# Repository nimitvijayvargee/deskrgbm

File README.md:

# deskrgbm
desktop rgb matrix for the vibes

deskrgbm has a xiao-rp2040 and a WS2812B matrix that can be controlled using QMK-Vial. It is a simple RGB Matrix that can display effects and be used as a desktop ornament. It also features a rotary encoder to control the effects, brightness and speed of the RGB Matrix. The code is written in QMK and can be easily modified using the Vial GUI.

The PCB is very easy to assemble and uses THT Capacitors to be beginner friendly. It is a simple 2 Layer board that does not cost too much to manufacture. The holder is designed in a way such that you can easily use heatsunk threaded inserts and M3 screws to hold the PCB in place. It is intended to print in PLA to be cost effective. \

## Bill of Materials

|Product       |Price|Link                                                                                               |
|--------------|-----|---------------------------------------------------------------------------------------------------|
|PCB           |21   |https://lioncircuits.com/                                                                          |
|WS2812B       |5    |https://www.ktron.in/product/ws2812b-rgb-smd-5050-led/                                             |
|THT Capacitors|5    |https://sharvielectronics.com/product/100nf-250v-0-1uf-polyester-film-capacitor-7-5mm              |
|Xiao RP2040   |8    |https://thinkrobotics.com/products/seeed-studio-xiao-rp2040                                        |
|Rotary encoder|3    |https://amzn.in/d/0EOqh1U                                                                          |
|Total         |42   |                                                                                                   |

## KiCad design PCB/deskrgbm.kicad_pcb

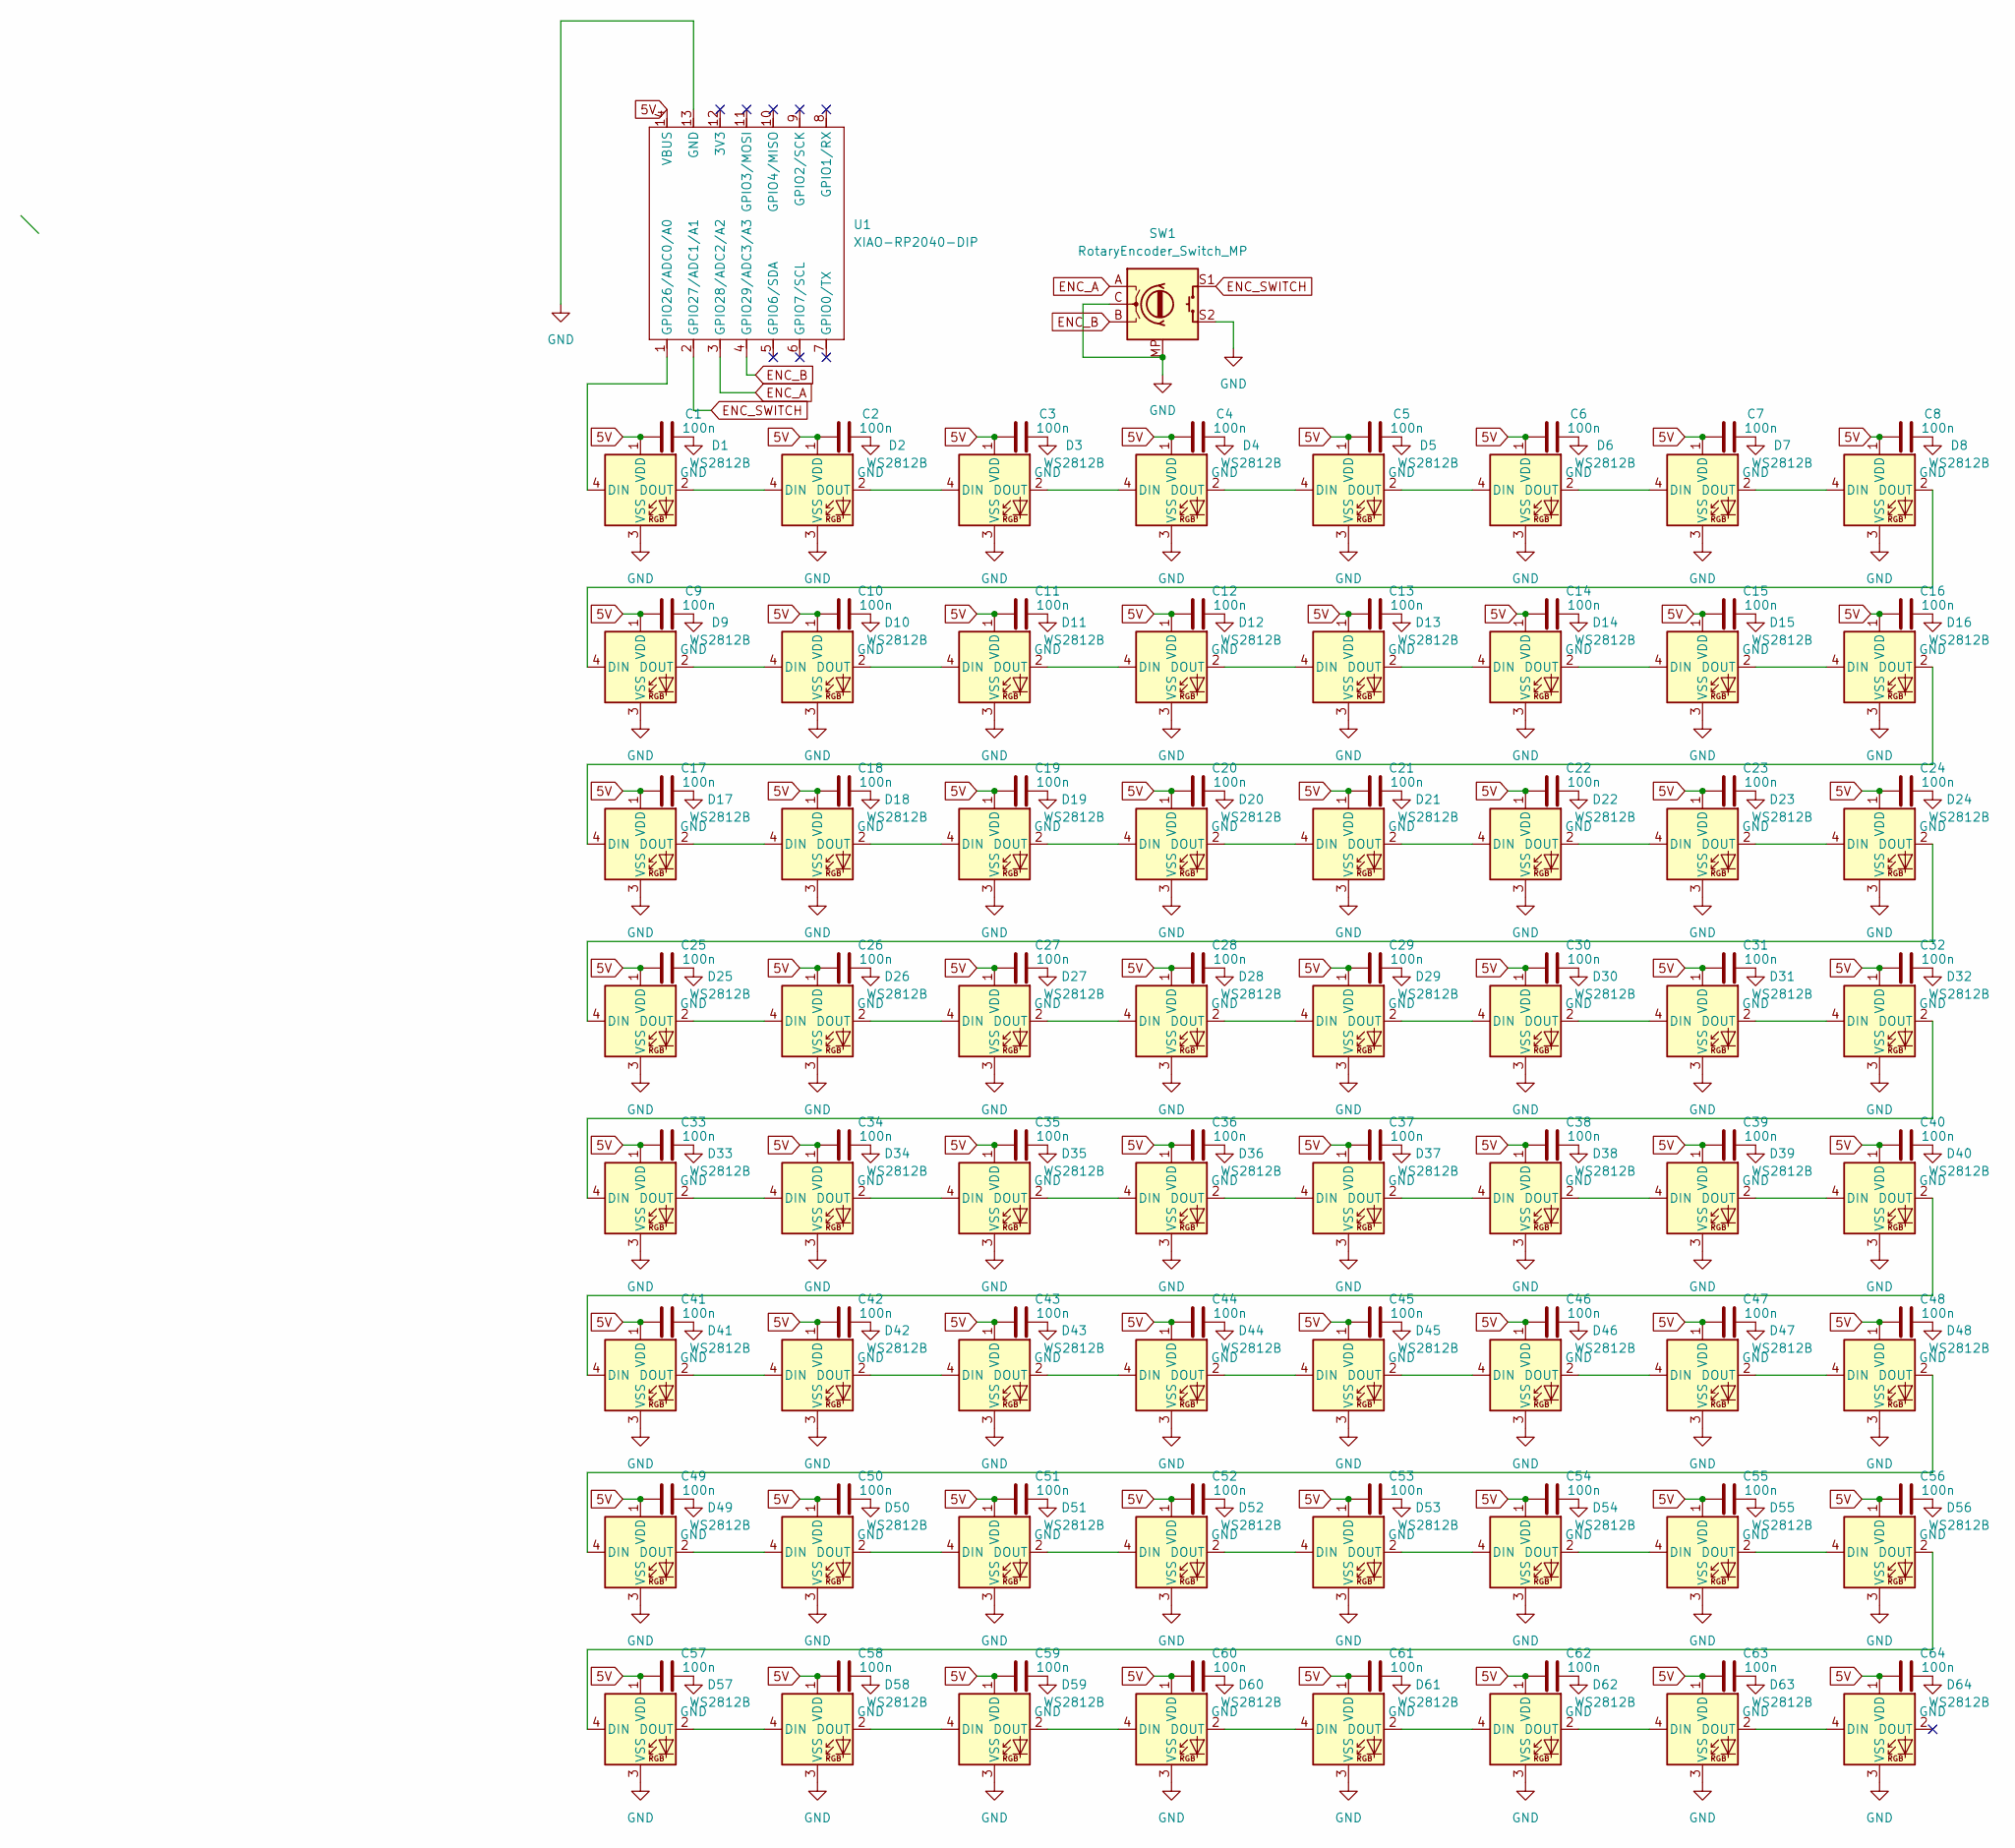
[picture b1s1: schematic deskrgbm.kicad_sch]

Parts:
C1, C2, C3, C4, C5, C6, C7, C8, C9, C10, C11, C12, C13, C14, C15, C16, C17, C18, C19, C20, C21, C22, C23, C24, C25, C26, C27, C28, C29, C30, C31, C32, C33, C34, C35, C36, C37, C38, C39, C40, C41, C42, C43, C44, C45, C46, C47, C48, C49, C50, C51, C52, C53, C54, C55, C56, C57, C58, C59, C60, C61, C62, C63, C64: 100n; C_Disc_D3.0mm_W1.6mm_P2.50mm
D1, D2, D3, D4, D5, D6, D7, D8, D9, D10, D11, D12, D13, D14, D15, D16, D17, D18, D19, D20, D21, D22, D23, D24, D25, D26, D27, D28, D29, D30, D31, D32, D33, D34, D35, D36, D37, D38, D39, D40, D41, D42, D43, D44, D45, D46, D47, D48, D49, D50, D51, D52, D53, D54, D55, D56, D57, D58, D59, D60, D61, D62, D63, D64: WS2812B; LED_WS2812B_PLCC4_5.0x5.0mm_P3.2mm
SW1: RotaryEncoder_Switch_MP; RotaryEncoder_Alps_EC11E-Switch_Vertical_H20mm_MountingHoles
U1: XIAO-RP2040-DIP

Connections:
5V: C1.2, C2.2, C3.2, C4.2, C5.2, C6.2, C7.2, C8.2, C9.2, C10.2, C11.2, C12.2, C13.2, C14.2, C15.2, C16.2, C17.2, C18.2, C19.2, C20.2, C21.2, C22.2, C23.2, C24.2, C25.2, C26.2, C27.2, C28.2, C29.2, C30.2, C31.2, C32.2, C33.2, C34.2, C35.2, C36.2, C37.2, C38.2, C39.2, C40.2, C41.2, C42.2, C43.2, C44.2, C45.2, C46.2, C47.2, C48.2, C49.2, C50.2, C51.2, C52.2, C53.2, C54.2, C55.2, C56.2, C57.2, C58.2, C59.2, C60.2, C61.2, C62.2, C63.2, C64.2, D1.1 (VDD), D2.1 (VDD), D3.1 (VDD), D4.1 (VDD), D5.1 (VDD), D6.1 (VDD), D7.1 (VDD), D8.1 (VDD), D9.1 (VDD), D10.1 (VDD), D11.1 (VDD), D12.1 (VDD), D13.1 (VDD), D14.1 (VDD), D15.1 (VDD), D16.1 (VDD), D17.1 (VDD), D18.1 (VDD), D19.1 (VDD), D20.1 (VDD), D21.1 (VDD), D22.1 (VDD), D23.1 (VDD), D24.1 (VDD), D25.1 (VDD), D26.1 (VDD), D27.1 (VDD), D28.1 (VDD), D29.1 (VDD), D30.1 (VDD), D31.1 (VDD), D32.1 (VDD), D33.1 (VDD), D34.1 (VDD), D35.1 (VDD), D36.1 (VDD), D37.1 (VDD), D38.1 (VDD), D39.1 (VDD), D40.1 (VDD), D41.1 (VDD), D42.1 (VDD), D43.1 (VDD), D44.1 (VDD), D45.1 (VDD), D46.1 (VDD), D47.1 (VDD), D48.1 (VDD), D49.1 (VDD), D50.1 (VDD), D51.1 (VDD), D52.1 (VDD), D53.1 (VDD), D54.1 (VDD), D55.1 (VDD), D56.1 (VDD), D57.1 (VDD), D58.1 (VDD), D59.1 (VDD), D60.1 (VDD), D61.1 (VDD), D62.1 (VDD), D63.1 (VDD), D64.1 (VDD), U1.14 (VBUS)
ENC_A: SW1.A, U1.3 (GPIO28/ADC2/A2)
ENC_B: SW1.B, U1.4 (GPIO29/ADC3/A3)
ENC_SWITCH: SW1.S1, U1.2 (GPIO27/ADC1/A1)
GND: C1.1, C2.1, C3.1, C4.1, C5.1, C6.1, C7.1, C8.1, C9.1, C10.1, C11.1, C12.1, C13.1, C14.1, C15.1, C16.1, C17.1, C18.1, C19.1, C20.1, C21.1, C22.1, C23.1, C24.1, C25.1, C26.1, C27.1, C28.1, C29.1, C30.1, C31.1, C32.1, C33.1, C34.1, C35.1, C36.1, C37.1, C38.1, C39.1, C40.1, C41.1, C42.1, C43.1, C44.1, C45.1, C46.1, C47.1, C48.1, C49.1, C50.1, C51.1, C52.1, C53.1, C54.1, C55.1, C56.1, C57.1, C58.1, C59.1, C60.1, C61.1, C62.1, C63.1, C64.1, D1.3 (VSS), D2.3 (VSS), D3.3 (VSS), D4.3 (VSS), D5.3 (VSS), D6.3 (VSS), D7.3 (VSS), D8.3 (VSS), D9.3 (VSS), D10.3 (VSS), D11.3 (VSS), D12.3 (VSS), D13.3 (VSS), D14.3 (VSS), D15.3 (VSS), D16.3 (VSS), D17.3 (VSS), D18.3 (VSS), D19.3 (VSS), D20.3 (VSS), D21.3 (VSS), D22.3 (VSS), D23.3 (VSS), D24.3 (VSS), D25.3 (VSS), D26.3 (VSS), D27.3 (VSS), D28.3 (VSS), D29.3 (VSS), D30.3 (VSS), D31.3 (VSS), D32.3 (VSS), D33.3 (VSS), D34.3 (VSS), D35.3 (VSS), D36.3 (VSS), D37.3 (VSS), D38.3 (VSS), D39.3 (VSS), D40.3 (VSS), D41.3 (VSS), D42.3 (VSS), D43.3 (VSS), D44.3 (VSS), D45.3 (VSS), D46.3 (VSS), D47.3 (VSS), D48.3 (VSS), D49.3 (VSS), D50.3 (VSS), D51.3 (VSS), D52.3 (VSS), D53.3 (VSS), D54.3 (VSS), D55.3 (VSS), D56.3 (VSS), D57.3 (VSS), D58.3 (VSS), D59.3 (VSS), D60.3 (VSS), D61.3 (VSS), D62.3 (VSS), D63.3 (VSS), D64.3 (VSS), SW1.C, SW1.MP, SW1.S2, U1.13 (GND)
unnamed: D1.4 (DIN), U1.1 (GPIO26/ADC0/A0)
unnamed: D1.2 (DOUT), D2.4 (DIN)
unnamed: D2.2 (DOUT), D3.4 (DIN)
unnamed: D3.2 (DOUT), D4.4 (DIN)
unnamed: D4.2 (DOUT), D5.4 (DIN)
unnamed: D5.2 (DOUT), D6.4 (DIN)
unnamed: D6.2 (DOUT), D7.4 (DIN)
unnamed: D7.2 (DOUT), D8.4 (DIN)
unnamed: D8.2 (DOUT), D9.4 (DIN)
unnamed: D9.2 (DOUT), D10.4 (DIN)
unnamed: D10.2 (DOUT), D11.4 (DIN)
unnamed: D11.2 (DOUT), D12.4 (DIN)
unnamed: D12.2 (DOUT), D13.4 (DIN)
unnamed: D13.2 (DOUT), D14.4 (DIN)
unnamed: D14.2 (DOUT), D15.4 (DIN)
unnamed: D15.2 (DOUT), D16.4 (DIN)
unnamed: D16.2 (DOUT), D17.4 (DIN)
unnamed: D17.2 (DOUT), D18.4 (DIN)
unnamed: D18.2 (DOUT), D19.4 (DIN)
unnamed: D19.2 (DOUT), D20.4 (DIN)
unnamed: D20.2 (DOUT), D21.4 (DIN)
unnamed: D21.2 (DOUT), D22.4 (DIN)
unnamed: D22.2 (DOUT), D23.4 (DIN)
unnamed: D23.2 (DOUT), D24.4 (DIN)
unnamed: D24.2 (DOUT), D25.4 (DIN)
unnamed: D25.2 (DOUT), D26.4 (DIN)
unnamed: D26.2 (DOUT), D27.4 (DIN)
unnamed: D27.2 (DOUT), D28.4 (DIN)
unnamed: D28.2 (DOUT), D29.4 (DIN)
unnamed: D29.2 (DOUT), D30.4 (DIN)
unnamed: D30.2 (DOUT), D31.4 (DIN)
unnamed: D31.2 (DOUT), D32.4 (DIN)
unnamed: D32.2 (DOUT), D33.4 (DIN)
unnamed: D33.2 (DOUT), D34.4 (DIN)
unnamed: D34.2 (DOUT), D35.4 (DIN)
unnamed: D35.2 (DOUT), D36.4 (DIN)
unnamed: D36.2 (DOUT), D37.4 (DIN)
unnamed: D37.2 (DOUT), D38.4 (DIN)
unnamed: D38.2 (DOUT), D39.4 (DIN)
unnamed: D39.2 (DOUT), D40.4 (DIN)
unnamed: D40.2 (DOUT), D41.4 (DIN)
unnamed: D41.2 (DOUT), D42.4 (DIN)
unnamed: D42.2 (DOUT), D43.4 (DIN)
unnamed: D43.2 (DOUT), D44.4 (DIN)
unnamed: D44.2 (DOUT), D45.4 (DIN)
unnamed: D45.2 (DOUT), D46.4 (DIN)
unnamed: D46.2 (DOUT), D47.4 (DIN)
unnamed: D47.2 (DOUT), D48.4 (DIN)
unnamed: D48.2 (DOUT), D49.4 (DIN)
unnamed: D49.2 (DOUT), D50.4 (DIN)
unnamed: D50.2 (DOUT), D51.4 (DIN)
unnamed: D51.2 (DOUT), D52.4 (DIN)
unnamed: D52.2 (DOUT), D53.4 (DIN)
unnamed: D53.2 (DOUT), D54.4 (DIN)
unnamed: D54.2 (DOUT), D55.4 (DIN)
unnamed: D55.2 (DOUT), D56.4 (DIN)
unnamed: D56.2 (DOUT), D57.4 (DIN)
unnamed: D57.2 (DOUT), D58.4 (DIN)
unnamed: D58.2 (DOUT), D59.4 (DIN)
unnamed: D59.2 (DOUT), D60.4 (DIN)
unnamed: D60.2 (DOUT), D61.4 (DIN)
unnamed: D61.2 (DOUT), D62.4 (DIN)
unnamed: D62.2 (DOUT), D63.4 (DIN)
unnamed: D63.2 (DOUT), D64.4 (DIN)

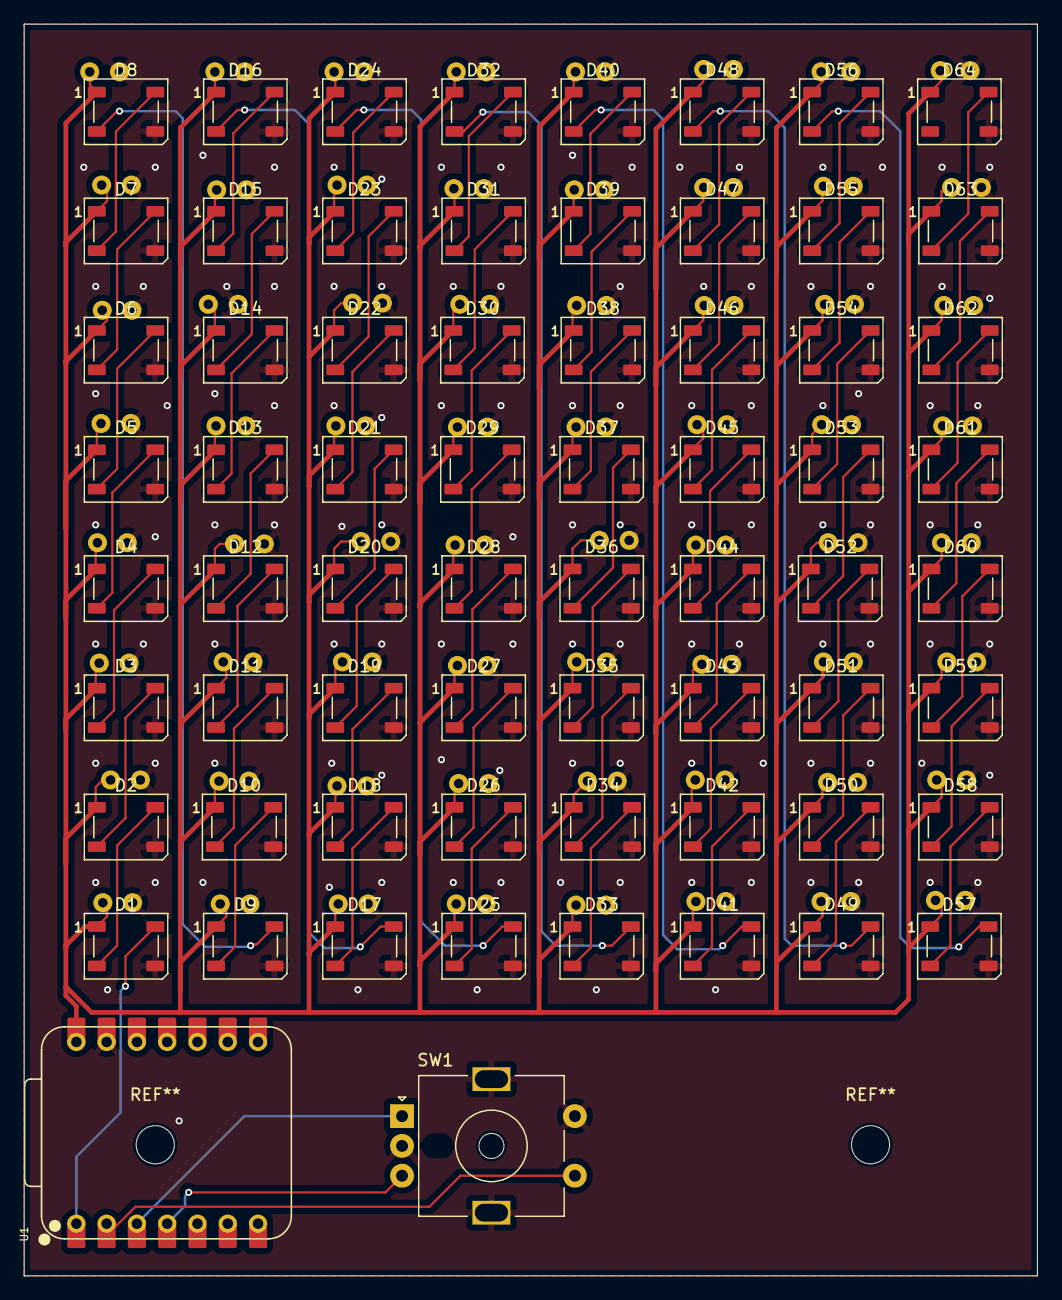
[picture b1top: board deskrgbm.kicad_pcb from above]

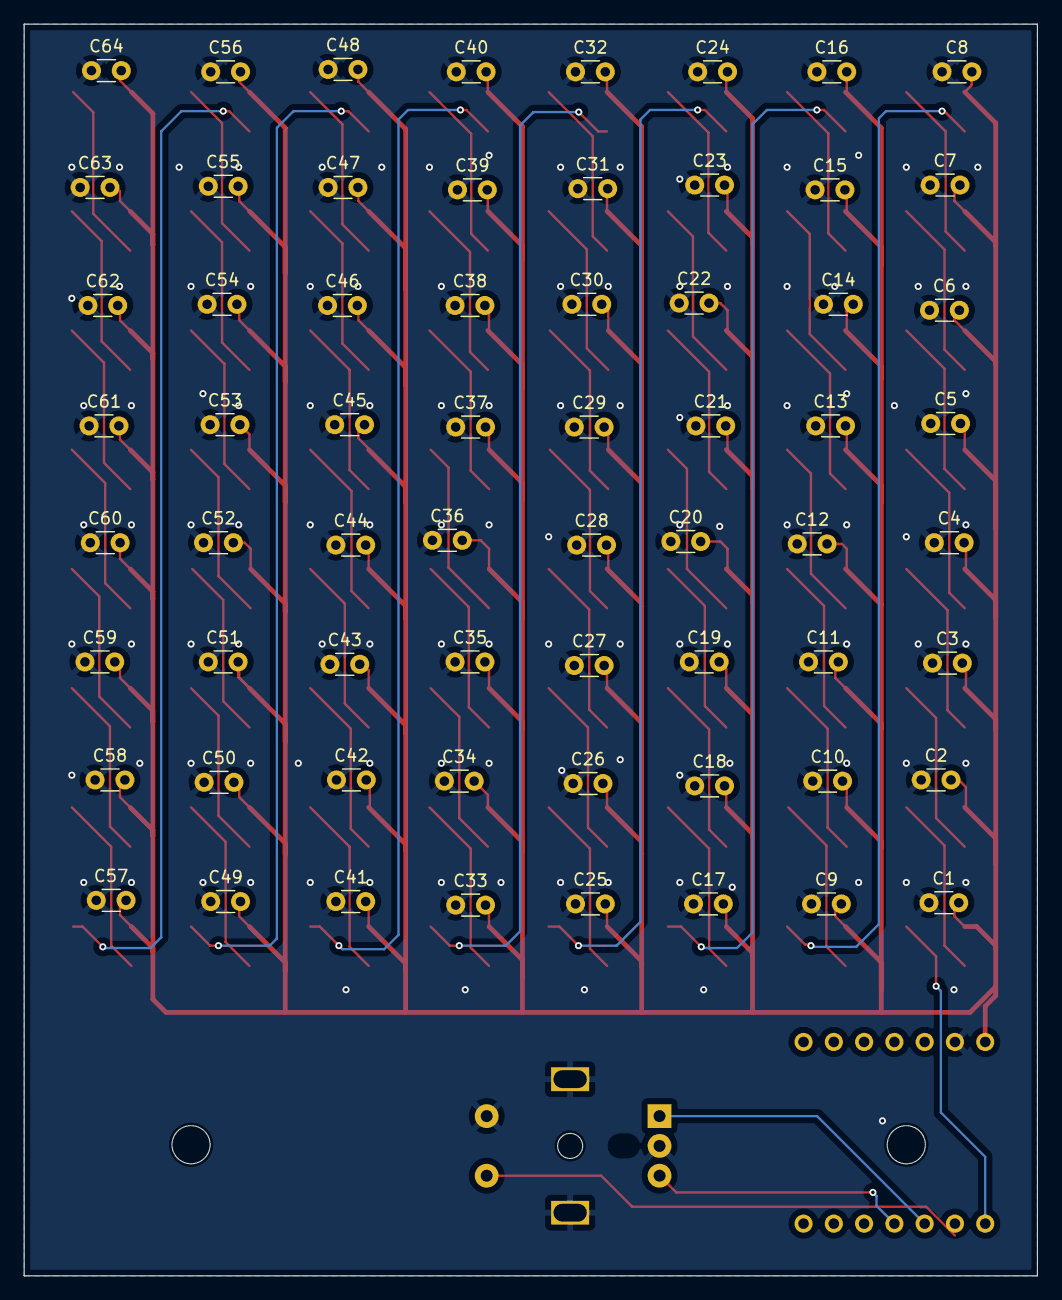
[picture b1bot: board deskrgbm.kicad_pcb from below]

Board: 2 copper layers, 85.0 x 105.0 mm, 130 parts (64 on the bottom side), 69 nets.

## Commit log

2025-07-25 Journal + PCB
2025-07-26 Journal + Firmware
2025-07-27 Journal + CAD
2025-07-27 Added BOM and updated journal
2025-07-27 Fix BOM
2025-07-29 Add assembly
